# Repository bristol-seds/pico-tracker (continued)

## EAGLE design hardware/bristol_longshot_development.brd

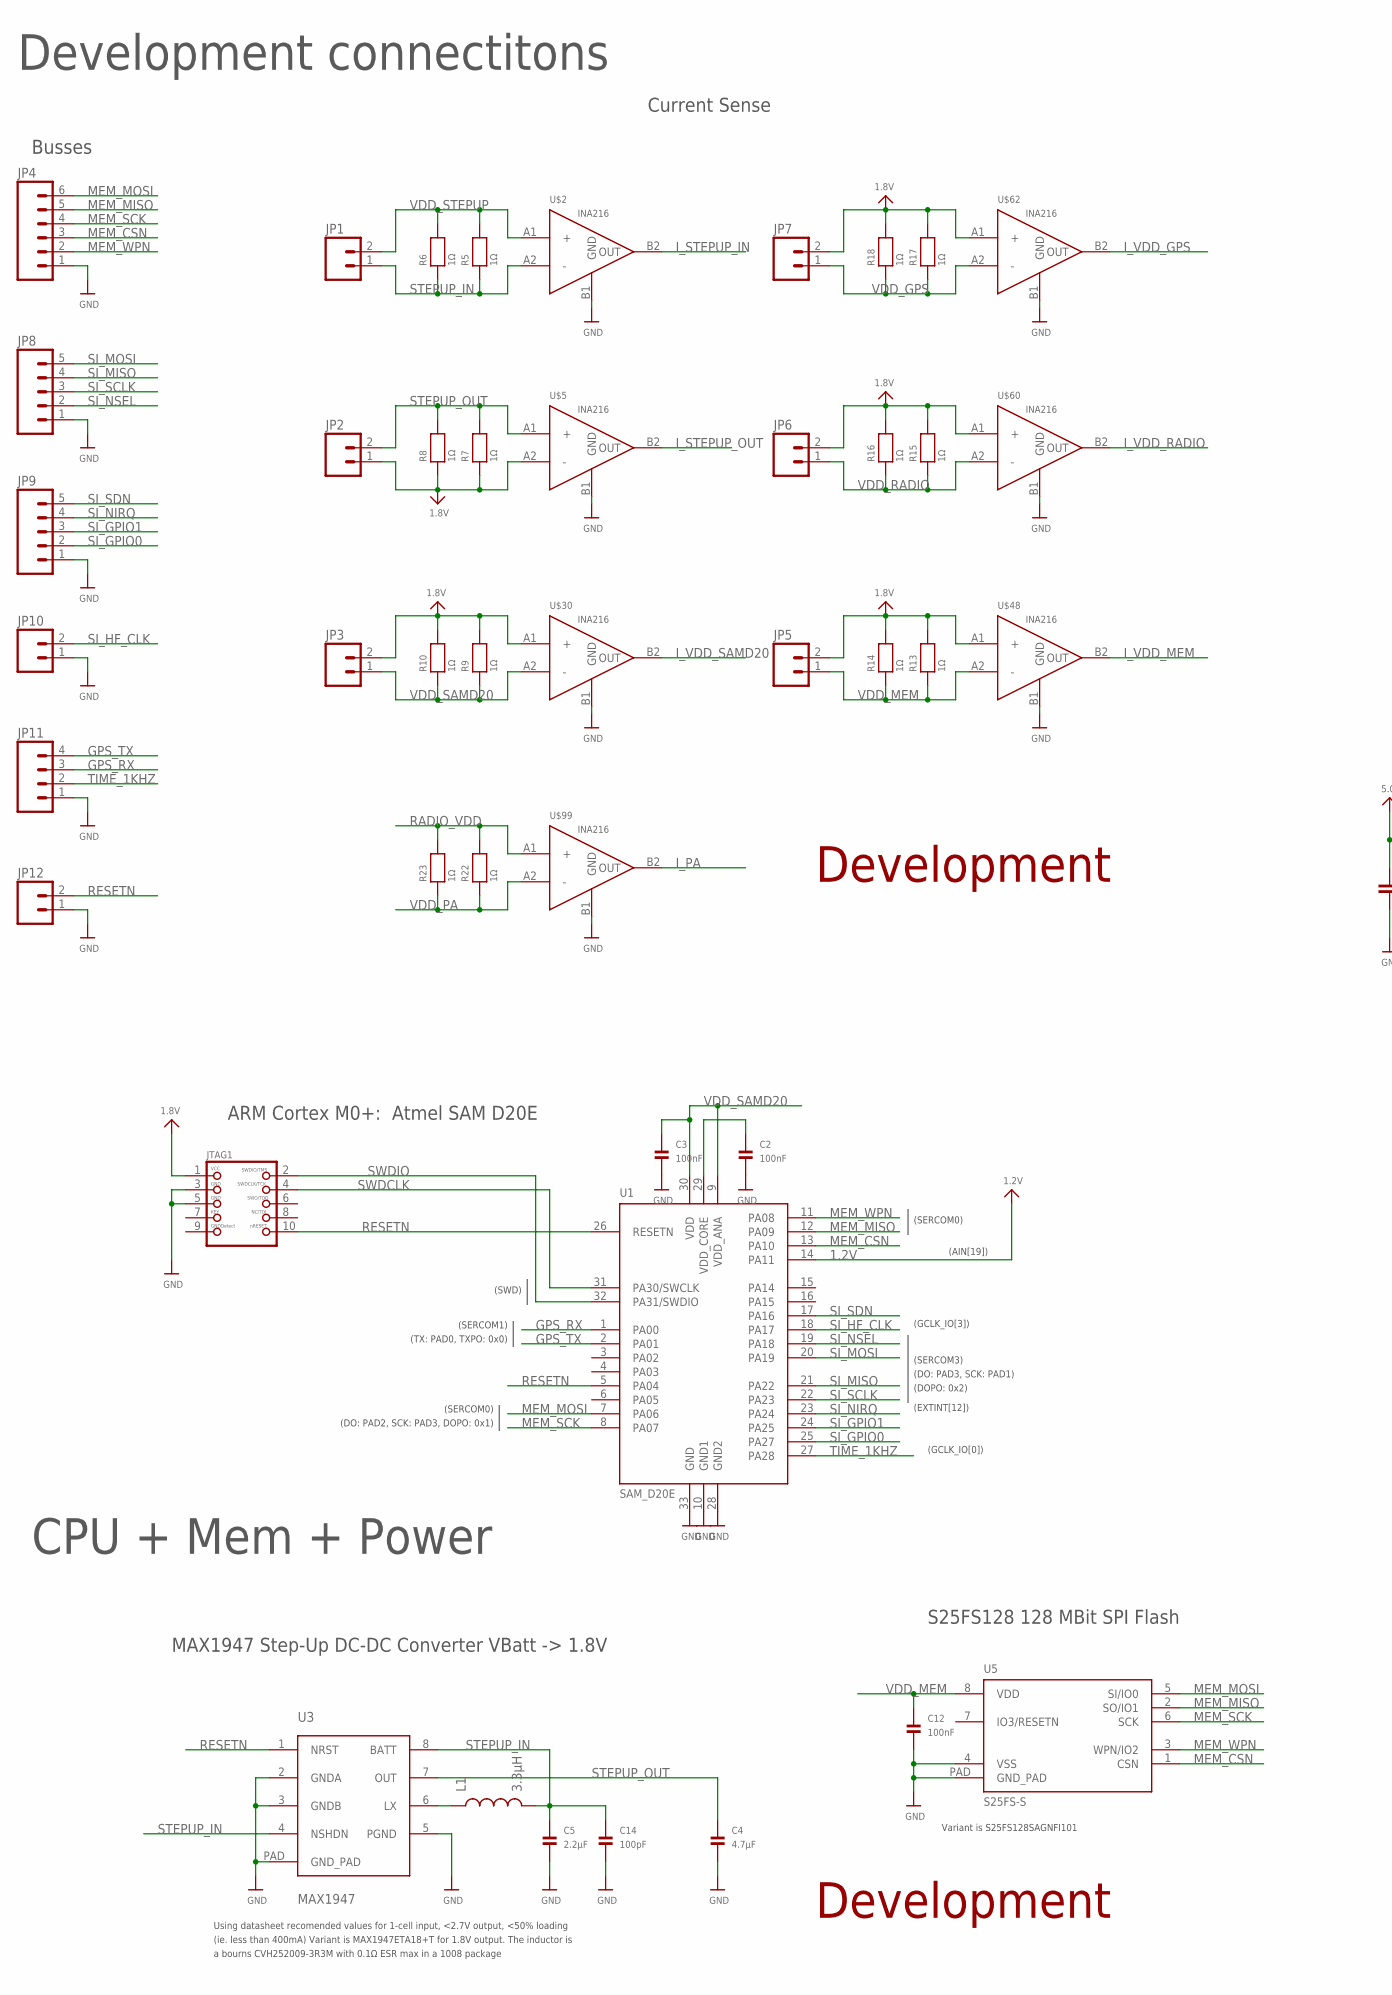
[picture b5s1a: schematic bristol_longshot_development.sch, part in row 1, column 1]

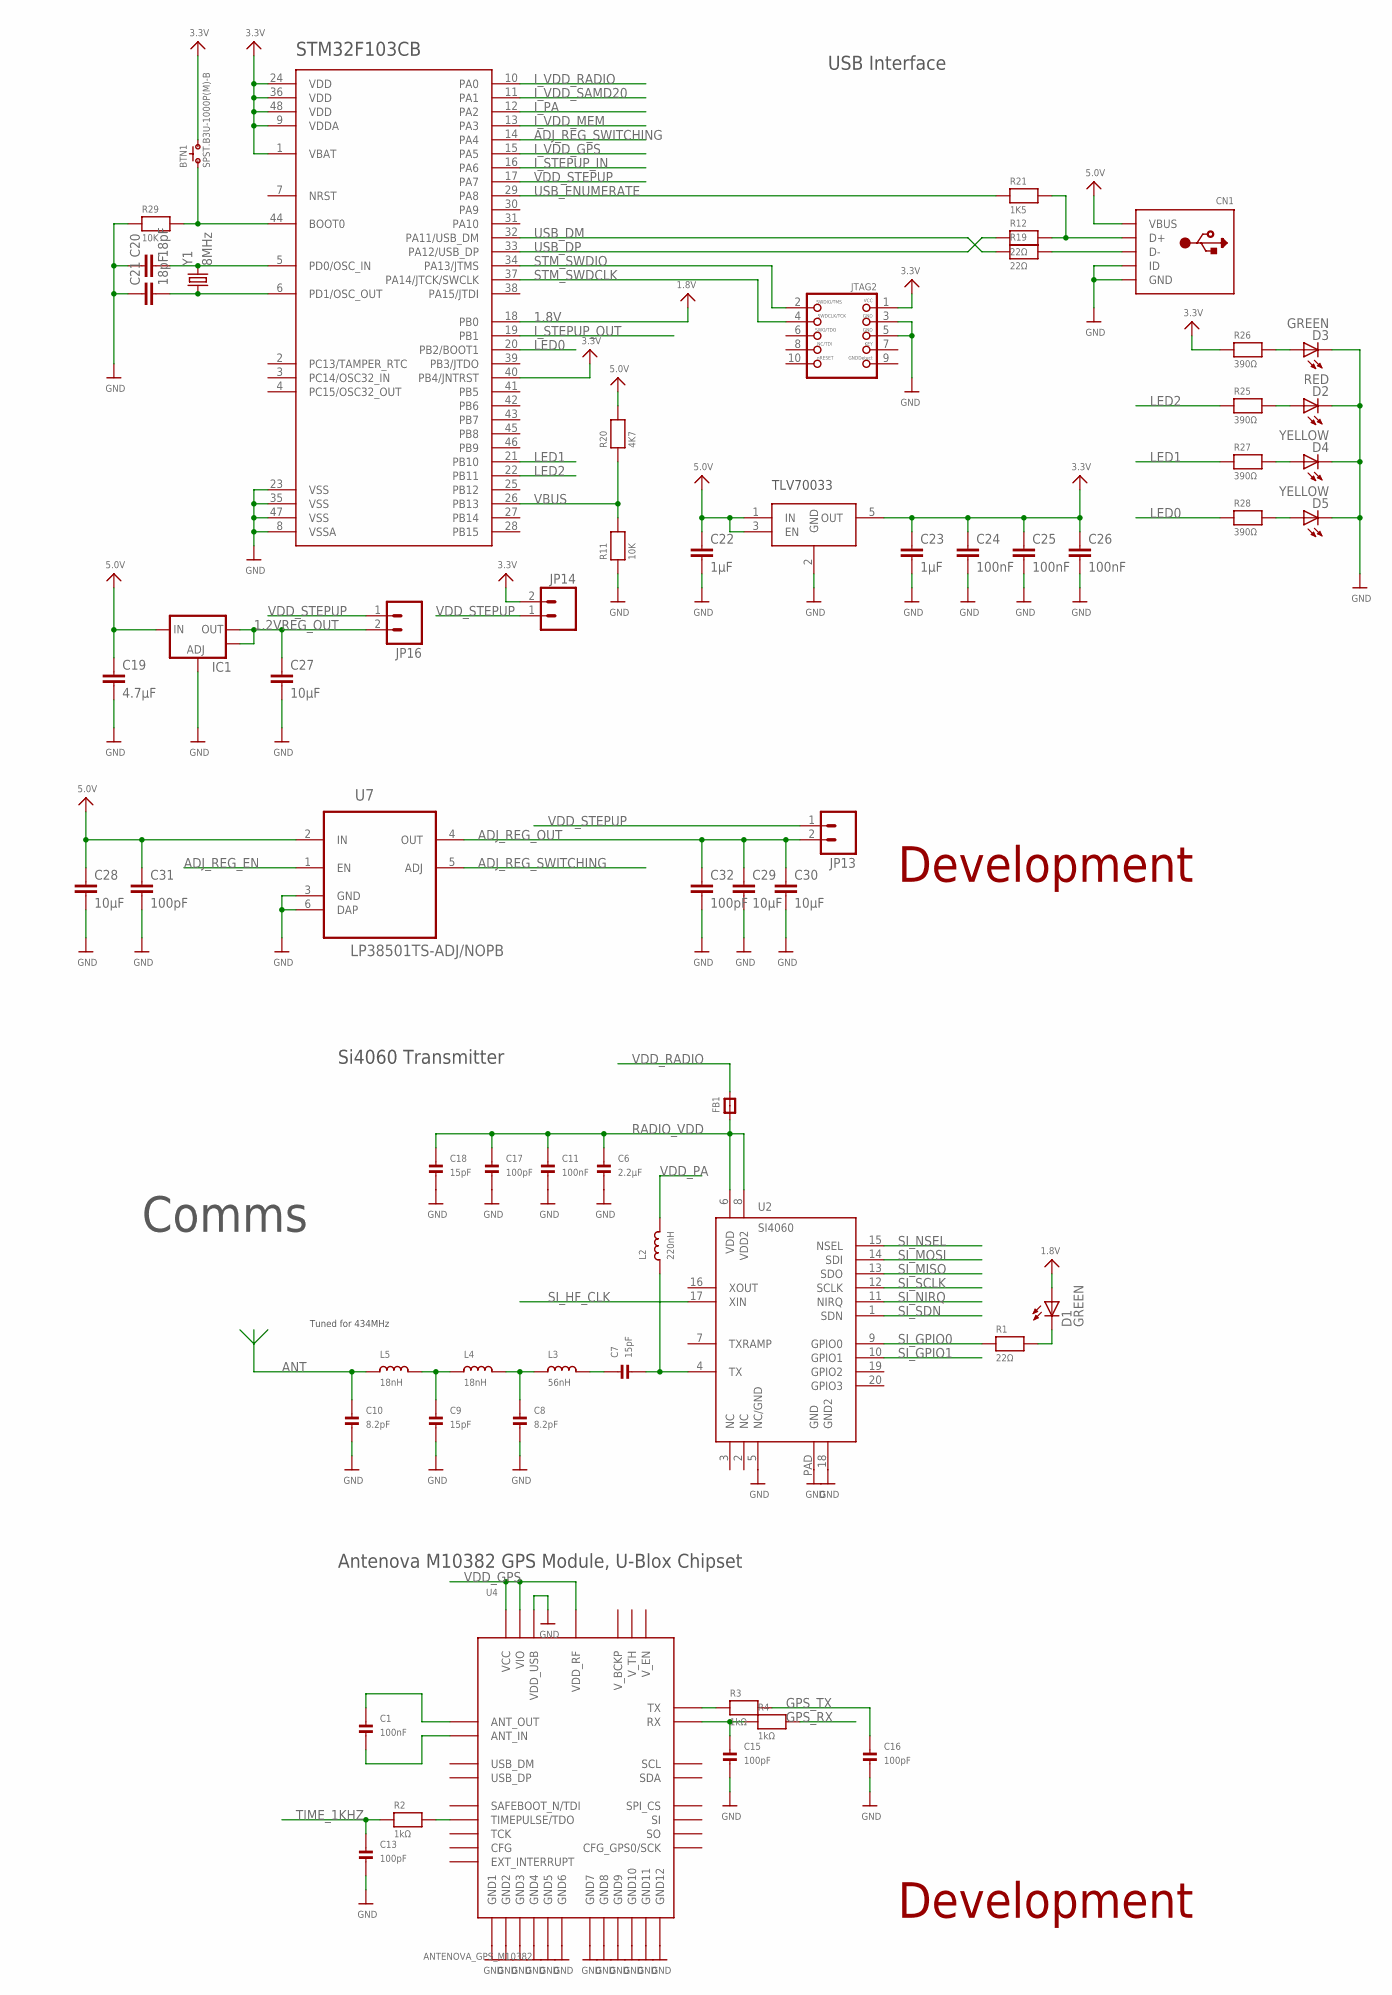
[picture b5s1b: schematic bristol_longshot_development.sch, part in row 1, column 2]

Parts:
BTN1: SPST.B3U-1000P(M)-B; B3U-1000P(M)-B
C1, C2, C3, C11, C12: 100nF; _0402
C4: 4.7µF; _0402
C5, C6: 2.2µF; _0402
C7, C9, C18: 15pF; _0402
C8, C10: 8.2pF; _0402
C13, C14, C15, C16, C17: 100pF; _0402
C19: 4.7µF; C0603K
C20, C21: 18pF; C0603K
C22, C23: 1µF; C0603K
C24, C25, C26: 100nF; C0603K
C27, C28, C29, C30: 10µF; C0603K
C31, C32: 100pF; C0603K
CN1: USBMINIB; USB-MINIB
D1, D3: GREEN; CHIPLED_0603
D2: RED; CHIPLED_0603
D4, D5: YELLOW; CHIPLED_0603
FB1: FERRITE_0402; _0402
IC1: V_REG_LM1117SOT223; SOT223
IC3: TLV70033DCK; SC70-5L
JP1, JP2, JP3, JP5, JP6, JP7, JP10, JP12, JP13, JP14, JP16: M02LOCK; 1X02_LOCK
JP4: M06LOCK; 1X06_LOCK
JP8, JP9: M05LOCK; 1X05_LOCK
JP11: M04LOCK; 1X04_LOCK
JTAG1, JTAG2: JTAG-CORTEXM3SMT; 2X05_1.27MM_SMT
L1: 3.3µH; 1007
L2: 220nH; _0402
L3: 56nH; _0402
L4, L5: 18nH; _0402
R1: 22Ω; _0402
R2, R3, R4: 1kΩ; _0402
R5, R6, R7, R8, R9, R10, R13, R14, R15, R16, R17, R18, R22, R23: 1Ω; _0402
R11, R29: 10K; 0603-MINI
R12, R19: 22Ω; 0603-MINI
R20: 4K7; 0603-MINI
R21: 1K5; 0603-MINI
R25, R26, R27, R28: 390Ω; 0603-MINI
U1: SAM_D20E; QFN32_5MM
U2: SI4060; QFN20
U3: MAX1947; TDFN8
U4: ANTENOVA_GPS_M10382
U5: S25FS-S; WSON8
U6: STM32F_48PIN; TQFP48
U7: LP38501TS-ADJ/NOPB; TO170P1435X457-6N
U$2, U$5, U$30, U$48, U$60, U$62, U$99: INA216; WCSP-4
Y1: 8MHz; CRYSTAL-SMD-5X3

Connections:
1.2V: U1.14 (PA11)
1.2VREG_OUT: C27.1, IC1.2 (OUT), IC1.4 (OUT), JP16.2
1.8V: D1.A, JP2.1, JP3.2, JP5.2, JP6.2, JP7.2, JTAG1.1, R7.1, R8.1, R9.2, R10.2, R13.2, R14.2, R15.2, R16.2, R17.2, R18.2, U6.18 (PB0), U$5.A2 (-), U$30.A1 (+), U$48.A1 (+), U$60.A1 (+), U$62.A1 (+)
3.3V: BTN1.2, C23.1, C24.1, C25.1, C26.1, IC3.5 (OUT), JP14.2, JTAG2.1, R26.1, U6.1 (VBAT), U6.9 (VDDA), U6.24 (VDD), U6.36 (VDD), U6.40 (PB4/JNTRST), U6.48 (VDD)
5.0V: C19.1, C22.1, C28.1, C31.1, CN1.VBUS, IC1.3 (IN), IC3.1 (IN), IC3.3 (EN), R20.2, U7.2 (IN)
ADJ_REG_EN: U7.1 (EN)
ADJ_REG_OUT: C29.1, C30.1, C32.1, JP13.2, U7.4 (OUT)
ADJ_REG_SWITCHING: U6.14 (PA4), U7.5 (ADJ)
ANT: C10.1, L5.1
AN_GPS_RX: C15.1, R4.1, U4.13_RX (RX)
AN_GPS_TX: R3.1, U4.11_TX (TX)
BOOT0: BTN1.1, R29.2, U6.44 (BOOT0)
D+: CN1.D+, R12.2, R21.2
D-: CN1.D-, R19.2
FILTER1: C8.1, L3.1, L4.2
FILTER2: C9.1, L4.1, L5.2
GND: C2.2, C3.2, C4.2, C5.2, C6.2, C8.2, C9.2, C10.2, C11.2, C12.2, C13.2, C14.2, C15.2, C16.2, C17.2, C18.2, C19.2, C20.1, C21.1, C22.2, C23.2, C24.2, C25.2, C26.2, C27.2, C28.2, C29.2, C30.2, C31.2, C32.2, CN1.GND, CN1.ID, D2.C, D3.C, D4.C, D5.C, IC1.1 (ADJ), IC3.2 (GND), JP4.1, JP8.1, JP9.1, JP10.1, JP11.1, JP12.1, JTAG1.3, JTAG1.5, JTAG2.3, JTAG2.5, R11.1, R29.1, U1.10 (GND1), U1.28 (GND2), U1.33 (GND), U2.5 (NC/GND), U2.18 (GND2), U2.PAD (GND), U3.2 (GNDA), U3.3 (GNDB), U3.5 (PGND), U3.PAD (GND_PAD), U4.2_GND (GND1), U4.4_GND (GND2), U4.14_GND (GND3), U4.17_GND (GND4), U4.21_GND (GND5), U4.24_GND (GND6), U4.26_GND (GND7), U4.28_GND (GND8), U4.32_VDD_USB (VDD_USB), U4.33_GND (GND9), U4.34_GND (GND10), U4.35_GND (GND11), U4.36_GND (GND12), U5.4 (VSS), U5.PAD (GND_PAD), U6.8 (VSSA), U6.23 (VSS), U6.35 (VSS), U6.47 (VSS), U7.3 (GND), U7.6 (DAP), U$2.B1 (GND), U$5.B1 (GND), U$30.B1 (GND), U$48.B1 (GND), U$60.B1 (GND), U$62.B1 (GND), U$99.B1 (GND)
GPS_ANT_IN: C1.2, U4.1_ANT_IN (ANT_IN)
GPS_ANT_OUT: C1.1, U4.3_ANT_OUT (ANT_OUT)
GPS_RX: JP11.3, R4.2, U1.1 (PA00)
GPS_TX: C16.1, JP11.4, R3.2, U1.2 (PA01)
I_PA: U6.12 (PA2), U$99.B2 (OUT)
I_STEPUP_IN: U6.16 (PA6), U$2.B2 (OUT)
I_STEPUP_OUT: U6.19 (PB1), U$5.B2 (OUT)
I_VDD_GPS: U6.15 (PA5), U$62.B2 (OUT)
I_VDD_MEM: U6.13 (PA3), U$48.B2 (OUT)
I_VDD_RADIO: U6.10 (PA0), U$60.B2 (OUT)
I_VDD_SAMD20: U6.11 (PA1), U$30.B2 (OUT)
LED0: R28.1, U6.20 (PB2/BOOT1)
LED1: R27.1, U6.21 (PB10)
LED2: R25.1, U6.22 (PB11)
LED_RES: D1.C, R1.2
LPC_XTAL2: C21.2, U6.6 (PD1/OSC_OUT), Y1.1
LX: L1.1, U3.6 (LX)
MEM_CSN: JP4.3, U1.13 (PA10), U5.1 (CSN)
MEM_MISO: JP4.5, U1.12 (PA09), U5.2 (SO/IO1)
MEM_MOSI: JP4.6, U1.7 (PA06), U5.5 (SI/IO0)
MEM_SCK: JP4.4, U1.8 (PA07), U5.6 (SCK)
MEM_WPN: JP4.2, U1.11 (PA08), U5.3 (WPN/IO2)
unnamed: D2.A, R25.2
unnamed: D3.A, R26.2
unnamed: D4.A, R27.2
unnamed: D5.A, R28.2
OSC_IN: C20.2, U6.5 (PD0/OSC_IN), Y1.3 (2)
RADIO_VDD: C6.1, C11.1, C17.1, C18.1, FB1.1, R22.2, R23.2, U2.6 (VDD), U2.8 (VDD2), U$99.A1 (+)
RESETN: JP12.2, JTAG1.10, U1.5 (PA04), U1.26 (RESETN), U3.1 (NRST)
RF_OUT: C7.2, L2.1, U2.4 (TX)
SI_GPIO0: JP9.2, R1.1, U1.25 (PA27), U2.9 (GPIO0)
SI_GPIO1: JP9.3, U1.24 (PA25), U2.10 (GPIO1)
SI_HF_CLK: JP10.2, U1.18 (PA17), U2.17 (XIN)
SI_MISO: JP8.4, U1.21 (PA22), U2.13 (SDO)
SI_MOSI: JP8.5, U1.20 (PA19), U2.14 (SDI)
SI_NIRQ: JP9.4, U1.23 (PA24), U2.11 (NIRQ)
SI_NSEL: JP8.2, U1.19 (PA18), U2.15 (NSEL)
SI_SCLK: JP8.3, U1.22 (PA23), U2.12 (SCLK)
SI_SDN: JP9.5, U1.17 (PA16), U2.1 (SDN)
STEPUP_IN: C5.1, C14.1, JP1.1, L1.2, R5.1, R6.1, U3.4 (NSHDN), U3.8 (BATT), U$2.A2 (-)
STEPUP_OUT: C4.1, JP2.2, R7.2, R8.2, U3.7 (OUT), U$5.A1 (+)
STM_SWDCLK: JTAG2.4, U6.37 (PA14/JTCK/SWCLK)
STM_SWDIO: JTAG2.2, U6.34 (PA13/JTMS)
SWDCLK: JTAG1.4, U1.31 (PA30/SWCLK)
SWDIO: JTAG1.2, U1.32 (PA31/SWDIO)
TANK: C7.1, L3.2
TIME_1KHZ: C13.1, JP11.2, R2.1, U1.27 (PA28)
TIME_1KHZ_DRIVE: R2.2, U4.23_TIMEPULSE/TDO (TIMEPULSE/TDO)
USB_DM: R19.1, U6.32 (PA11/USB_DM)
USB_DP: R12.1, U6.33 (PA12/USB_DP)
USB_ENUMERATE: R21.1, U6.29 (PA8)
VBUS: R11.2, R20.1, U6.26 (PB13)
VDD_CORE: C2.1, U1.29 (VDD_CORE)
VDD_GPS: JP7.1, R17.1, R18.1, U4.5_VIO (VIO), U4.25_VDD_RF (VDD_RF), U4.27_VCC (VCC), U$62.A2 (-)
VDD_MEM: C12.1, JP5.1, R13.1, R14.1, U5.8 (VDD), U$48.A2 (-)
VDD_PA: L2.2, R22.1, R23.1, U$99.A2 (-)
VDD_RADIO: FB1.2, JP6.1, R15.1, R16.1, U$60.A2 (-)
VDD_SAMD20: C3.1, JP3.1, R9.1, R10.1, U1.9 (VDD_ANA), U1.30 (VDD), U$30.A2 (-)
VDD_STEPUP: JP1.2, JP13.1, JP14.1, JP16.1, R5.2, R6.2, U6.17 (PA7), U$2.A1 (+)

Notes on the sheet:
ARM Cortex M0+: Atmel SAM D20E
(SERCOM3)
(SWD)
(GCLK_IO[0])
Using datasheet recomended values for 1-cell input, <2.7V output, <50% loading (ie. less than 400mA) Variant is MAX1947ETA18+T for 1.8V output. The inductor is a bourns CVH252009-3R3M with 0.1Ω ESR max in a 1008 package
(SERCOM0)
(EXTINT[12])
(DO: PAD3, SCK: PAD1)
(DOPO: 0x2)
(DO: PAD2, SCK: PAD3, DOPO: 0x1)
(GCLK_IO[3])
(SERCOM1)
(TX: PAD0, TXPO: 0x0)
MAX1947 Step-Up DC-DC Converter VBatt -> 1.8V
(AIN[19])
S25FS128 128 MBit SPI Flash
Variant is S25FS128SAGNFI101
Antenova M10382 GPS Module, U-Blox Chipset
Si4060 Transmitter
Tuned for 434MHz
CPU + Mem + Power
Comms
Development connectitons
Development
Current Sense
STM32F103CB
TLV70033
Busses
USB Interface

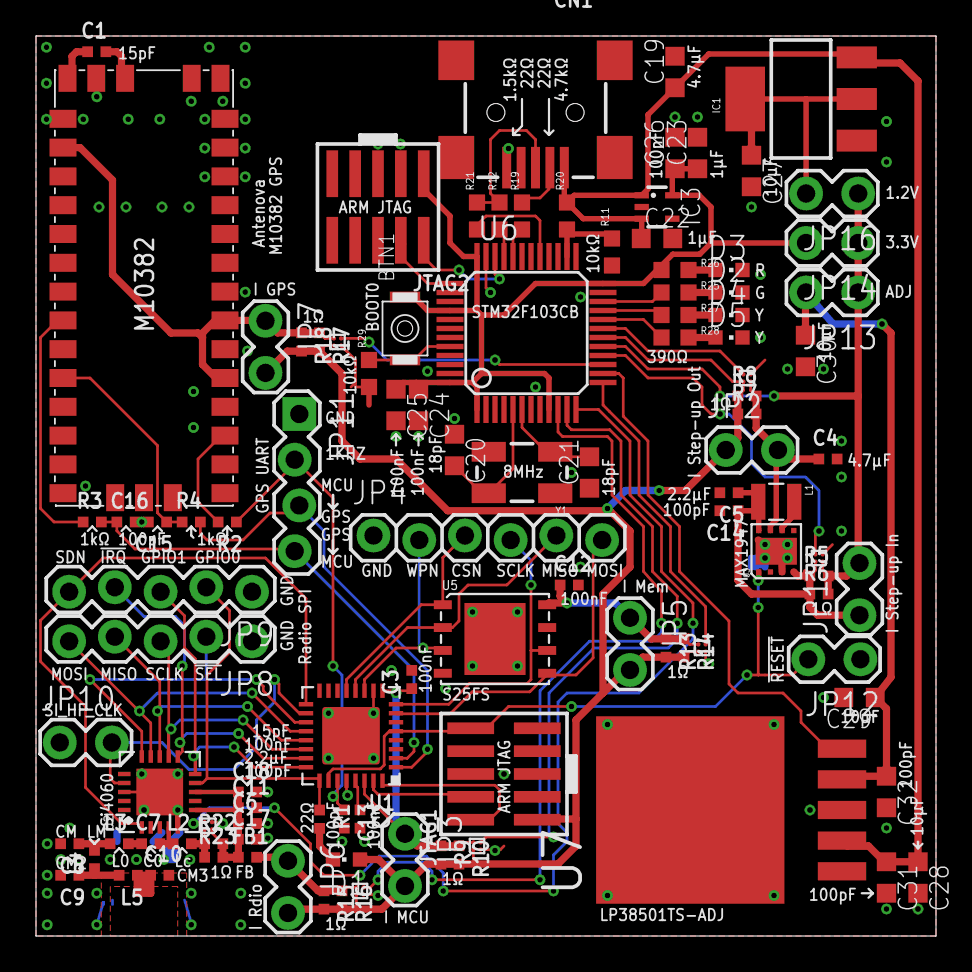
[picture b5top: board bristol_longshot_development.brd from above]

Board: 2 copper layers, 50.0 x 50.0 mm, 107 parts (0 on the bottom side), 74 nets.

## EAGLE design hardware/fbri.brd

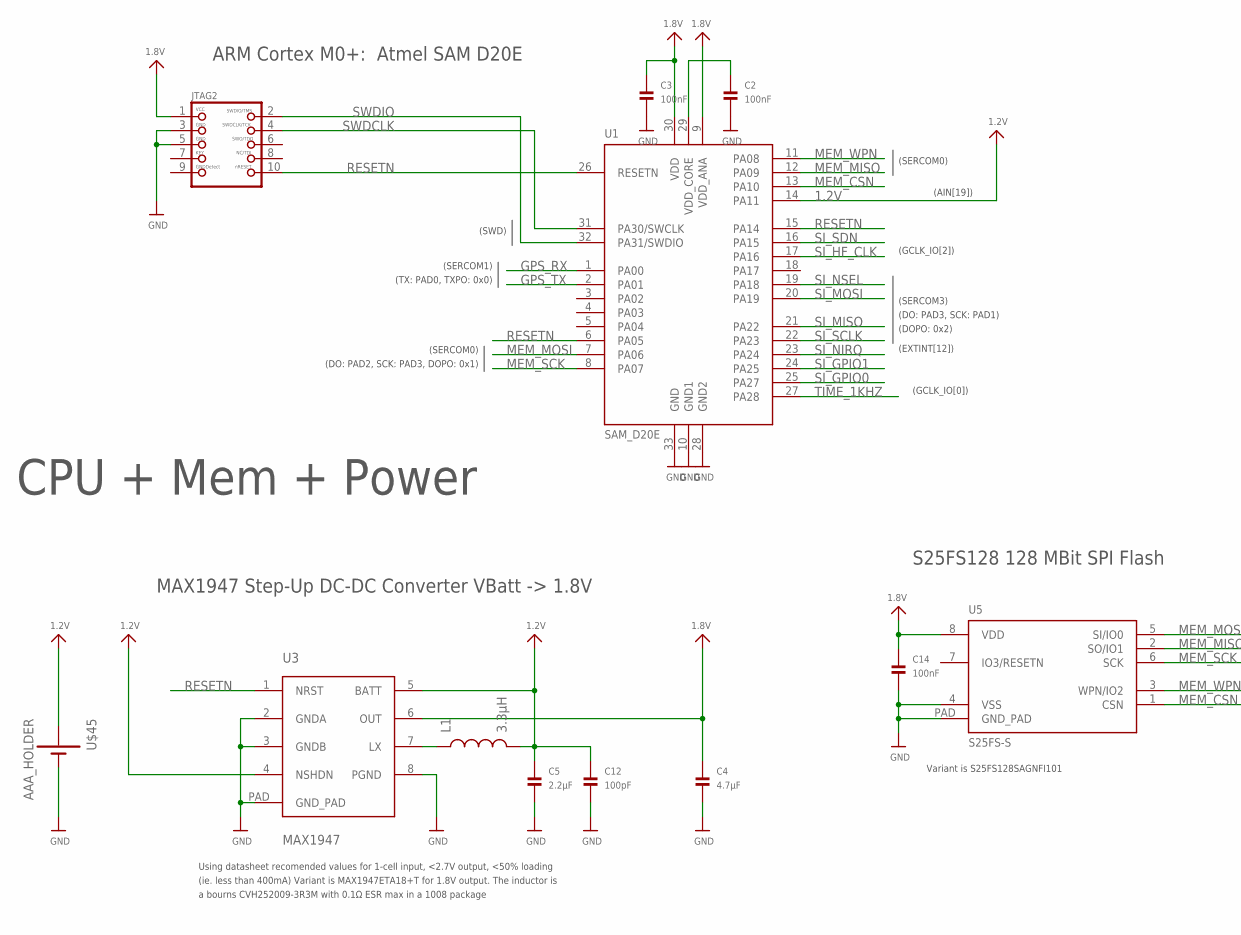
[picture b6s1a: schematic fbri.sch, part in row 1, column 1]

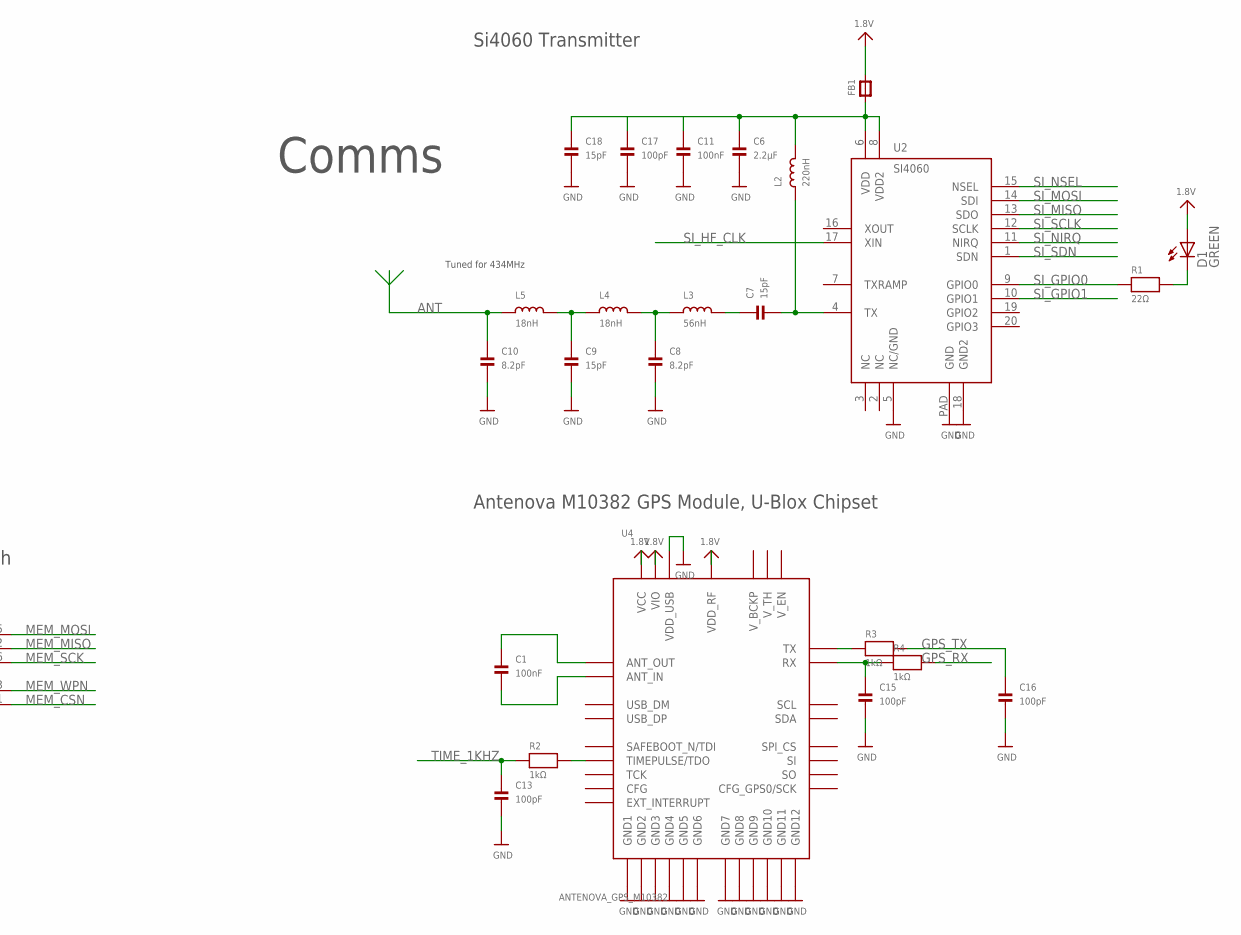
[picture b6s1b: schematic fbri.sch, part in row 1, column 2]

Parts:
C1, C2, C3, C11, C14: 100nF; _0402
C4: 4.7µF; _0402
C5, C6: 2.2µF; _0402
C7, C9, C18: 15pF; _0402
C8, C10: 8.2pF; _0402
C12, C13, C15, C16, C17: 100pF; _0402
D1: GREEN; CHIPLED_0603
FB1: FERRITE_0402; _0402
JTAG2: JTAG-CORTEXM3SMT; 2X05_1.27MM_SMT
L1: 3.3µH; 1007
L2: 220nH; _0402
L3: 56nH; _0402
L4, L5: 18nH; _0402
R1: 22Ω; _0402
R2, R3, R4: 1kΩ; _0402
U1: SAM_D20E; QFN32_5MM
U2: SI4060; QFN20
U3: MAX1947; TDFN8
U4: ANTENOVA_GPS_M10382
U5: S25FS-S; WSON8
U$45: AAA_HOLDER; AAA

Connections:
1.2V: C5.1, C12.1, L1.2, U1.14 (PA11), U3.4 (NSHDN), U3.5 (BATT), U$45.+2 (+)
1.8V: C3.1, C4.1, C14.1, D1.A, FB1.2, JTAG2.1, U1.9 (VDD_ANA), U1.30 (VDD), U3.6 (OUT), U4.5_VIO (VIO), U4.25_VDD_RF (VDD_RF), U4.27_VCC (VCC), U5.8 (VDD)
ANT: C10.1, L5.1
AN_GPS_RX: C15.1, R4.1, U4.13_RX (RX)
AN_GPS_TX: R3.1, U4.11_TX (TX)
FILTER1: C8.1, L3.1, L4.2
FILTER2: C9.1, L4.1, L5.2
GND: C2.2, C3.2, C4.2, C5.2, C6.2, C8.2, C9.2, C10.2, C11.2, C12.2, C13.2, C14.2, C15.2, C16.2, C17.2, C18.2, JTAG2.3, JTAG2.5, U1.10 (GND1), U1.28 (GND2), U1.33 (GND), U2.5 (NC/GND), U2.18 (GND2), U2.PAD (GND), U3.2 (GNDA), U3.3 (GNDB), U3.8 (PGND), U3.PAD (GND_PAD), U4.2_GND (GND1), U4.4_GND (GND2), U4.14_GND (GND3), U4.17_GND (GND4), U4.21_GND (GND5), U4.24_GND (GND6), U4.26_GND (GND7), U4.28_GND (GND8), U4.32_VDD_USB (VDD_USB), U4.33_GND (GND9), U4.34_GND (GND10), U4.35_GND (GND11), U4.36_GND (GND12), U5.4 (VSS), U5.PAD (GND_PAD), U$45.-1 (-), U$45.-2 (-)
GPS_ANT_IN: C1.2, U4.1_ANT_IN (ANT_IN)
GPS_ANT_OUT: C1.1, U4.3_ANT_OUT (ANT_OUT)
GPS_RX: R4.2, U1.1 (PA00)
GPS_TX: C16.1, R3.2, U1.2 (PA01)
LED_RES: D1.C, R1.2
LX: L1.1, U3.7 (LX)
MEM_CSN: U1.13 (PA10), U5.1 (CSN)
MEM_MISO: U1.12 (PA09), U5.2 (SO/IO1)
MEM_MOSI: U1.7 (PA06), U5.5 (SI/IO0)
MEM_SCK: U1.8 (PA07), U5.6 (SCK)
MEM_WPN: U1.11 (PA08), U5.3 (WPN/IO2)
RADIO_VDD: C6.1, C11.1, C17.1, C18.1, FB1.1, L2.2, U2.6 (VDD), U2.8 (VDD2)
RESETN: JTAG2.10, U1.6 (PA05), U1.15 (PA14), U1.26 (RESETN), U3.1 (NRST)
RF_OUT: C7.2, L2.1, U2.4 (TX)
SI_GPIO0: R1.1, U1.25 (PA27), U2.9 (GPIO0)
SI_GPIO1: U1.24 (PA25), U2.10 (GPIO1)
SI_HF_CLK: U1.17 (PA16), U2.17 (XIN)
SI_MISO: U1.21 (PA22), U2.13 (SDO)
SI_MOSI: U1.20 (PA19), U2.14 (SDI)
SI_NIRQ: U1.23 (PA24), U2.11 (NIRQ)
SI_NSEL: U1.19 (PA18), U2.15 (NSEL)
SI_SCLK: U1.22 (PA23), U2.12 (SCLK)
SI_SDN: U1.16 (PA15), U2.1 (SDN)
SWDCLK: JTAG2.4, U1.31 (PA30/SWCLK)
SWDIO: JTAG2.2, U1.32 (PA31/SWDIO)
TANK: C7.1, L3.2
TIME_1KHZ: C13.1, R2.1, U1.27 (PA28)
TIME_1KHZ_DRIVE: R2.2, U4.23_TIMEPULSE/TDO (TIMEPULSE/TDO)
VDD_CORE: C2.1, U1.29 (VDD_CORE)

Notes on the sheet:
ARM Cortex M0+: Atmel SAM D20E
(SERCOM3)
(SWD)
(GCLK_IO[0])
Using datasheet recomended values for 1-cell input, <2.7V output, <50% loading (ie. less than 400mA) Variant is MAX1947ETA18+T for 1.8V output. The inductor is a bourns CVH252009-3R3M with 0.1Ω ESR max in a 1008 package
(SERCOM0)
(EXTINT[12])
(DO: PAD3, SCK: PAD1)
(DOPO: 0x2)
(DO: PAD2, SCK: PAD3, DOPO: 0x1)
(GCLK_IO[2])
(SERCOM1)
(TX: PAD0, TXPO: 0x0)
MAX1947 Step-Up DC-DC Converter VBatt -> 1.8V
(AIN[19])
S25FS128 128 MBit SPI Flash
Variant is S25FS128SAGNFI101
Antenova M10382 GPS Module, U-Blox Chipset
Si4060 Transmitter
Tuned for 434MHz
CPU + Mem + Power
Comms

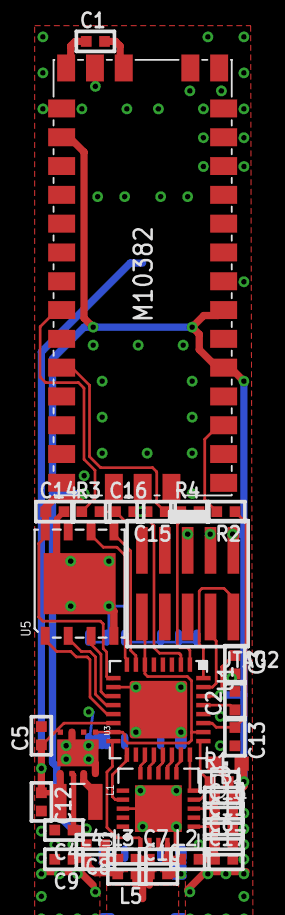
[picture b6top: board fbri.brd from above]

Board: 2 copper layers, 36 parts (1 on the bottom side), 37 nets.
